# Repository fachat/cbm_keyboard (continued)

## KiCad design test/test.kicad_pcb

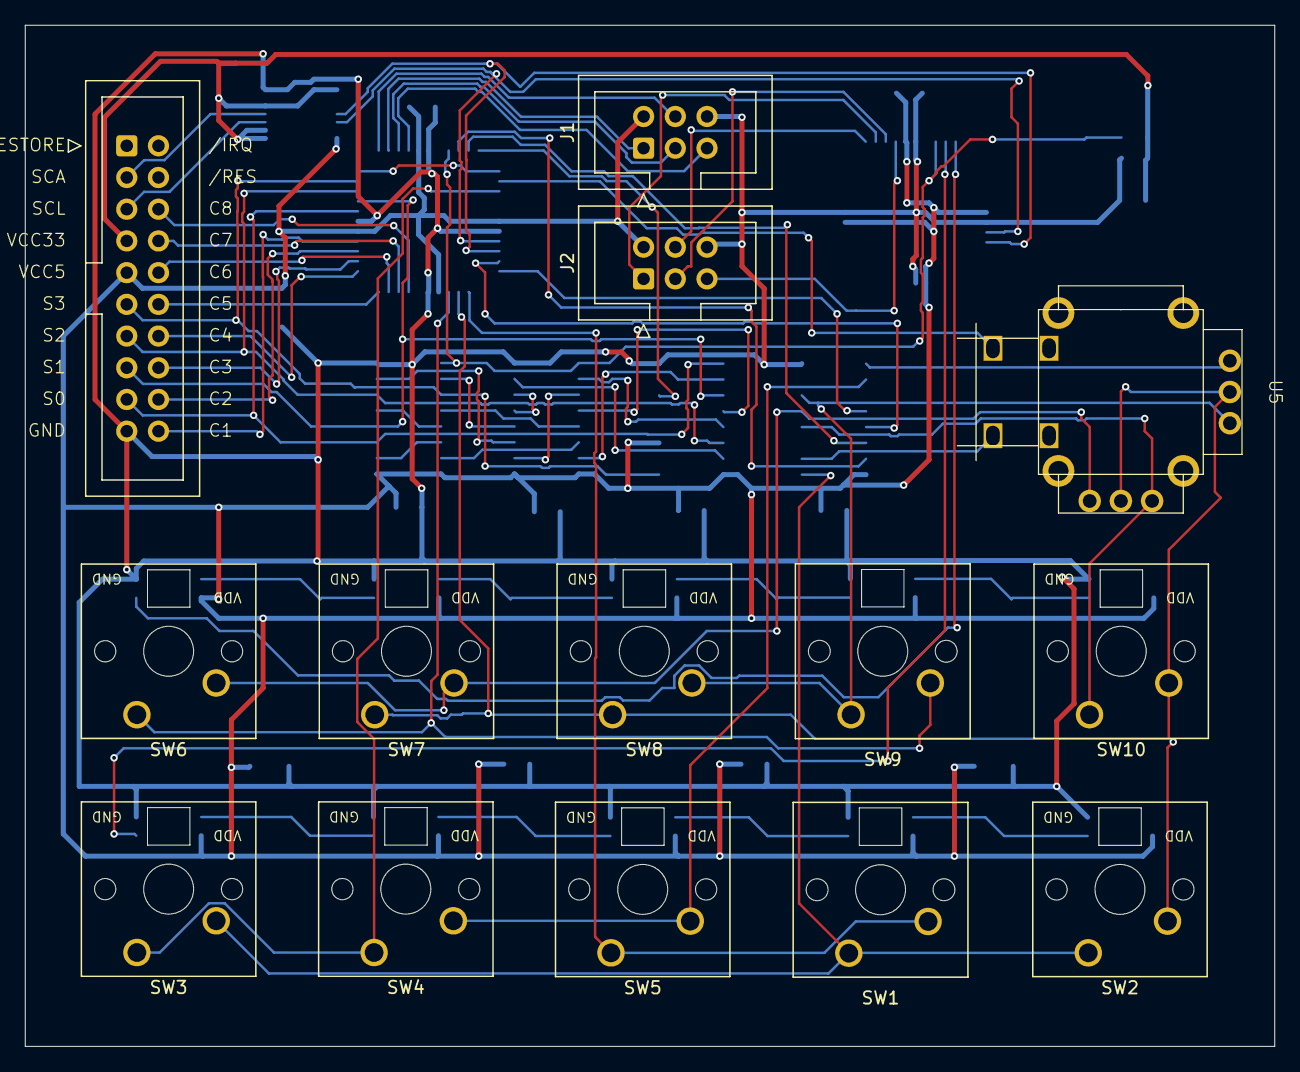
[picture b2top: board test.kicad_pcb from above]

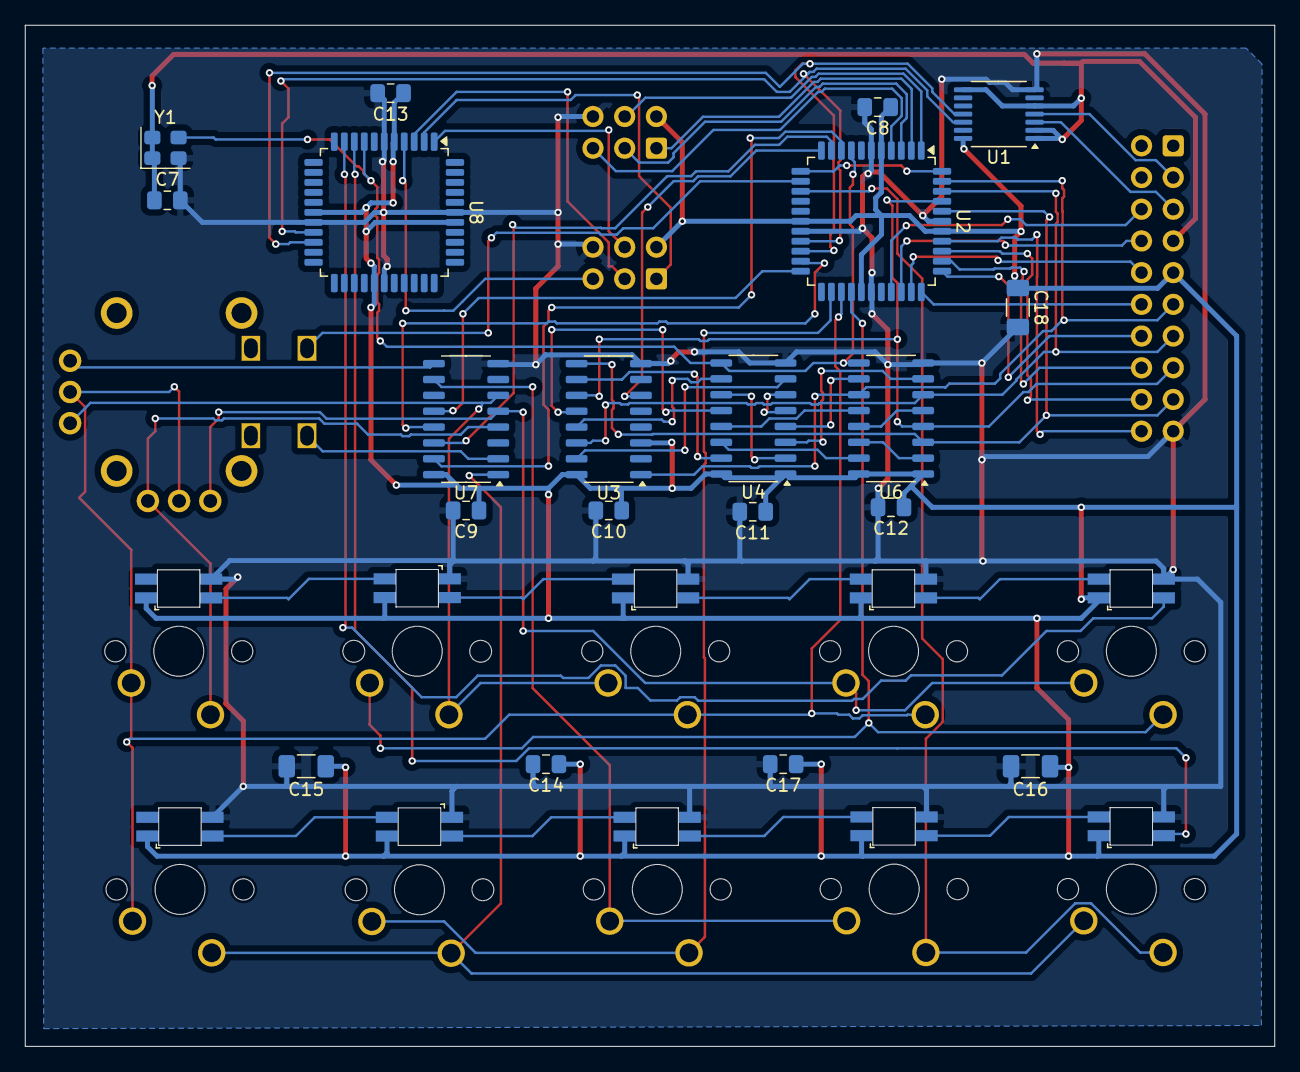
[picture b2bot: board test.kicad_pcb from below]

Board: 2 copper layers, 100.1 x 81.8 mm, 34 parts (20 on the bottom side), 68 nets.

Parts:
C7, C8, C9, C10, C11, C12, C13, C14, C17: 100n; C_0805_2012Metric_Pad1.18x1.45mm_HandSolder
C15, C16, C18: 100u; C_1206_3216Metric_Pad1.33x1.80mm_HandSolder
J1, J2: AVR-ISP-6; IDC-Header_2x03_P2.54mm_Vertical
J6: New_PET_keyboard_connector; PET_New_Keyboard_Connector
SW1, SW9: CherryMX_1.00u_PCB_LTST-A683CEGBW-Rotated
SW2, SW10: CherryMX_LTST-A683CEGBW; SW_Cherry_MX_1.00u_PCB_with_RGB_LED
SW3, SW4, SW5, SW6, SW7, SW8: SW_Cherry_MX_1.00u_PCB_with_RGB_LED
U1: LSF0204Q; TSSOP-14_4.4x5mm_P0.65mm
U2, U8: ATmega32A-A; TQFP-44_10x10mm_P0.8mm
U3: 74HCT85; SO-16_3.9x9.9mm_P1.27mm
U4, U6: 74LS174; SO-16_3.9x9.9mm_P1.27mm
U5: THB Miniature Thumbstick THB001P
U7: 74LS145; SO-16_3.9x9.9mm_P1.27mm
Y1: ASE-xxxMHz; Oscillator_SMD_Abracon_ASE-4Pin_3.2x2.5mm

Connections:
C1: J6.20 (C1), U2.37 (PA0)
C2: J6.19 (C2), U2.36 (PA1)
C3: J6.18 (C3), U2.35 (PA2)
C4: J6.17 (C4), U2.34 (PA3)
C5: J6.16 (C5), U2.33 (PA4)
C6: J6.15 (C6), U2.32 (PA5)
C7: J6.14 (C7), U2.31 (PA6)
C8: J6.13 (C8), U2.30 (PA7)
CLK16M: U2.8 (XTAL1), U4.9 (Cp), U6.9 (Cp), U8.8 (XTAL1), Y1.3 (OUT)
Col1: SW1.1, SW5.1, U2.24 (PC5)
Col2: SW2.2, SW7.1, SW8.1, SW10.2, U2.25 (PC6), U5.10 (LRCommon), U5.13 (UDCommon)
Col3: SW6.1, SW9.1, U2.26 (PC7)
Col4: U2.13 (PD4), U5.7 (SW2_A)
Col5: SW3.1, SW4.1, U2.14 (PD5)
GND: C7.2, C8.2, C9.2, C10.2, C11.2, C12.2, C13.2, C14.2, C15.2, C16.2, C17.2, C18.2, J1.6 (GND), J2.6 (GND), J6.21 (GND), SW1.3 (GND), SW2.3 (VSS), SW3.3 (GND), SW4.3 (GND), SW5.3 (GND), SW6.3 (GND), SW7.3 (GND), SW8.3 (GND), SW9.3 (GND), SW10.3 (VSS), U1.7 (GND), U2.6 (GND), U2.18 (GND), U2.28 (GND), U2.39 (GND), U3.8 (GND), U4.8 (GND), U6.8 (GND), U7.8 (GND), U8.6 (GND), U8.18 (GND), U8.28 (GND), U8.39 (GND), Y1.2 (GND)
unnamed: J1.1 (MISO), U2.2 (PB6)
unnamed: J1.4 (MOSI), U2.1 (PB5)
unnamed: J1.3 (SCK), U2.3 (PB7)
unnamed: J1.5 (~RST), U2.4 (~RESET)
unnamed: J2.1 (MISO), U8.2 (PB6)
unnamed: J2.4 (MOSI), U8.1 (PB5)
unnamed: J2.3 (SCK), U8.3 (PB7)
unnamed: J2.5 (~RST), U8.4 (~RESET)
unnamed: J6.29 (SCA), U1.4 (A3)
unnamed: J6.28 (SCL), U1.3 (A2)
unnamed: SW1.4 (DIN), SW5.5 (DOUT)
unnamed: SW1.5 (DOUT), SW2.4 (DIN)
unnamed: SW3.4 (DIN), U8.9 (PD0)
unnamed: SW3.5 (DOUT), SW4.4 (DIN)
unnamed: SW4.5 (DOUT), SW5.4 (DIN)
unnamed: SW6.4 (DIN), U8.10 (PD1)
unnamed: SW6.5 (DOUT), SW7.4 (DIN)
unnamed: SW7.5 (DOUT), SW8.4 (DIN)
unnamed: SW8.5 (DOUT), SW9.4 (DIN)
unnamed: SW9.5 (DOUT), SW10.4 (DIN)
unnamed: U2.12 (PD3), U2.44 (PB4)
unnamed: U2.21 (PC2), U7.13 (P2)
unnamed: U2.22 (PC3), U7.12 (P3)
unnamed: U2.9 (PD0), U7.15 (P0)
unnamed: U2.10 (PD1), U7.14 (P1)
unnamed: U2.11 (PD2), U3.6 (Oa=b)
unnamed: U3.10 (A0), U4.15 (Q5)
unnamed: U3.12 (A1), U4.12 (Q4)
unnamed: U3.13 (A2), U4.10 (Q3)
unnamed: U3.15 (A3), U4.7 (Q2)
unnamed: U4.3 (D0), U6.7 (Q2)
unnamed: U4.4 (D1), U6.10 (Q3)
unnamed: U4.5 (Q1), U4.6 (D2)
unnamed: U4.2 (Q0), U4.11 (D3)
unnamed: U4.13 (D4), U6.12 (Q4)
unnamed: U4.14 (D5), U6.15 (Q5)
unnamed: U6.5 (Q1), U6.13 (D4)
unnamed: U6.2 (Q0), U6.14 (D5)
Row0: SW1.2, SW2.1, SW3.2, U7.1 (Q0)
Row1: U5.8 (SW2_B), U7.2 (Q1)
Row3: SW10.1, U5.12 (Up), U7.4 (Q3)
Row4: SW6.2, SW7.2, U5.14 (Down), U7.5 (Q4)
Row5: SW8.2, SW9.2, U5.11 (Right), U7.6 (Q5)
Row7: U5.9 (Left), U7.9 (Q7)
Row8: SW4.2, SW5.2, U7.10 (Q8)
S0: J6.22 (S0), U2.40 (PB0), U3.9 (B0), U6.3 (D0)
S1: J6.23 (S1), U2.41 (PB1), U3.11 (B1), U6.4 (D1)
S2: J6.24 (S2), U2.42 (PB2), U3.14 (B2), U6.6 (D2)
S3: J6.25 (S3), U2.43 (PB3), U3.1 (B3), U6.11 (D3)
SCL: U1.12 (B2), U2.19 (PC0), U8.19 (PC0)
SDA: U1.11 (B3), U2.20 (PC1), U8.20 (PC1)
V33: C7.1, J6.27 (VCC33), U1.1 (VRefA), U1.2 (A1), U1.5 (A4), U1.8 (EN), Y1.1 (EN), Y1.4 (Vdd)
VCC: C8.1, C9.1, C10.1, C11.1, C12.1, C13.1, C14.1, C15.1, C16.1, C17.1, C18.1, J1.2 (VCC), J2.2 (VCC), J6.26 (VCC5), SW1.6 (VCC), SW2.6 (VDD), SW3.6 (VCC), SW4.6 (VCC), SW5.6 (VCC), SW6.6 (VCC), SW7.6 (VCC), SW8.6 (VCC), SW9.6 (VCC), SW10.6 (VDD), U1.14 (VRefB), U2.5 (VCC), U2.17 (VCC), U2.27 (AVCC), U2.38 (VCC), U3.3 (Ia=b), U3.16 (VCC), U4.1 (~Mr), U4.16 (VCC), U6.1 (~Mr), U6.16 (VCC), U7.16 (VCC), U8.5 (VCC), U8.17 (VCC), U8.27 (AVCC), U8.38 (VCC)

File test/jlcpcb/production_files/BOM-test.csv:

Comment,Designator,Footprint,LCSC,Quantity
ASE-xxxMHz,Y1,Oscillator_SMD_Abracon_ASE-4Pin_3.2x2.5mm,C12668,1
100n,"C10,C11,C12,C13,C14,C17,C7,C8,C9",C_0805_2012Metric_Pad1.18x1.45mm_HandSolder,C14663,9
100u,"C15,C16,C18",C_1206_3216Metric_Pad1.33x1.80mm_HandSolder,C15008,3
LSF0204Q,U1,TSSOP-14_4.4x5mm_P0.65mm,C2677502,1
~,U5,THB Miniature Thumbstick THB001P,C2685355,1
New_PET_keyboard_connector,J6,PET_New_Keyboard_Connector,C492444,1
~,"SW1,SW10,SW2,SW3,SW4,SW5,SW6,SW7,SW8,SW9",CherryMX_1.00u_PCB_LTST-A683CEGBW-Rotated,C5149201,10
AVR-ISP-6,"J1,J2",IDC-Header_2x03_P2.54mm_Vertical,C5372863,2
ATmega32A-A,"U2,U8",TQFP-44_10x10mm_P0.8mm,C5659,2
74HCT85,U3,SO-16_3.9x9.9mm_P1.27mm,C5953,1
74LS145,U7,SO-16_3.9x9.9mm_P1.27mm,C60829,1
74LS174,"U4,U6",SO-16_3.9x9.9mm_P1.27mm,C6828,2

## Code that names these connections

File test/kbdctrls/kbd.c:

#include <string.h>
#include <util/delay.h>
#include <avr/io.h>
#include <avr/interrupt.h>

#include "kbd.h"

unsigned char rowvals[16];

/*
 * Connection to the actual host
 */
void host_setup() {

	memset(rowvals, 0, 16);

	// disable UART (alt fun conflicts with I/O)
	UCSRB = 0;
	// JTAG needs to be disabled by HFUSE

	// port B0-3 is select lines in from host
	DDRB &= 0xf0;
	// no pullups
	PORTB &= 0xf0;
	// PB 5-7 are SPI prog lines, doubling as output to Host
	// test for moving PA0-7 to PB0-7
	DDRB &= 0x1f;
	// no pullups, set to output 0 when active to pull low
	PORTB & 0x1f;

	// PB4 is output to /RES when pulled low
	PORTB |= 0x10;
	DDRB |= 0x10;

	// PA is column out, using open-collector
	// no pullups. So, output is sent by
	// setting port to 0, and input.
	// then switching to output 
	// for those bits that should be pulled low
	DDRA = 0;
	PORTA = 0; 

	// interrupt handling
	// PD2 and PD3 are interrupt sources, PD2 is INT0 
	// and used as host select change int
	DDRD &= 0xfb;
	// no pullups
	PORTD &= 0xfb;

	// configure int0 on falling edge
	MCUCR = (MCUCR & 0xfc) | 0x02;
	// enable int0
	GICR |= 0x40;

	// own keyboard scan

	// row select bits 0/1
	DDRD |= 0x03;
	PORTD &= 0xfc;
	// row select bits 2/3
	DDRC |= 0x0c;
	PORTC &= 0xf3;

	// column value inputs
	// split on two ports due to needed alt functions for PC0/1, PD2

	// bits 0-3 are PC4-7, input with pullup
	DDRC &= 0x0f;
	PORTC |= 0xf0;
	// bits 4-7 are PD4-7, input with pullup
	DDRD &= 0x0f;
	PORTD |= 0xf0;

	// set PA0 to analog input,

	// AREF = AVCC
	// left adjust so we only need to use the
	// high byte with 8 bit resolution
	ADMUX = 0x60;
	// enable ADC, single ended PA0
	ADCSRA = 0x80;

	sei();
}

/*
 * note this ISR sets DDRA in less than 2.3us
 * which is very much enough for a 1-4 MHz PET scan routine
 * but not for a 13.5 MHz speed machine. 
 *
 * The normal scan reads the byte, then compares it again.
 * The first read happens on cycle 8 after change, the second on cycle 11.
 * See $e4be and following in the BASIC 4
 *
 * So, we have 11 cycles at 13.5 MHz, or 810ns only to write the correct
 * value ...
 *
 */
ISR( INT0_vect ) {
	DDRA = rowvals[PINB & 0x0f] & 0xfe;
	//PORTD ^= 0x01;
}

void kbd_scan() {
	for (unsigned char row = 0; row < 16; row++) {
		// set row selector
		PORTD = (PORTD & 0xfc) | (row & 0x03);
		PORTC = (PORTC & 0xf3) | (row & 0x0c);

		// read col values for row
		unsigned char v = 0;
		unsigned char ind = PIND;
		unsigned char inc = PINC;
		v = (ind & 0xf0) | ((inc >> 4) & 0x0f);

		v |= 3; 

		rowvals[row] = v ^ 255;
	}
}

void check_res() {
	// check RES
	if (rowvals[9] & 0x20) {
		// res low
		PORTB &= 0xef;
	} else {
		PORTB |= 0x10;
	}
}

void joy_scan() {
	// prescaler 7 = 1/128 = 125kHz
	ADCSRA = 0x87;

	//start conversion
	ADCSRA |= 1 << ADSC;

	while (!(ADCSRA & 0x10)) {
		// ADIF set
	
		// we use left adjust, so only high byte needed	
		unsigned char val = ADCH;

		// max value is 0xff
		// mid value is 0x80
		// low water we define as 0x40
		// high water we set to 0xc0
		if (val < 0x40) {
			// set crsr down
			rowvals[1] |= 0x40;
			// set ">" 
			//rowvals[8] |= 0x10;
		} else
		if (val > 0xc0) {
			// set crsr up
			rowvals[1] |= 0x40;
			rowvals[8] |= 0x20;
			// set "<" 
			//rowvals[9] |= 0x08;
		}
	}	

}

void main() {

	host_setup();

	// fake key for test
	//rowvals[1] = 0x01;

	while (1) {
		kbd_scan();
		joy_scan();
		check_res();
		_delay_ms(10);
	}
}

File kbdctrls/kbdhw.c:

#include <string.h>
#include <util/delay.h>
#include <avr/io.h>
#include <avr/interrupt.h>

#include "kbdhw.h"
#include "map.h"

unsigned char scanvals[16];
static unsigned char rowvals[16];

/*
 * Connection to the actual host
 */
void host_setup() {

	memset(rowvals, 0, 16);

	// disable UART (alt fun conflicts with I/O)
	UCSRB = 0;
	// JTAG needs to be disabled by HFUSE

	// port A0-3 is select lines in from host
	DDRA &= 0xf0;
	// no pullups
	PORTA &= 0xf0;

	// PB 0-7 are "open collector" outputs; 
	// i.e. only set to output 0 when active, otherwise input
	// PB 5-7 are SPI prog lines, doubling as output to Host
	DDRB &= 0x00;
	// no pullups, set to output 0 when active to pull low
	PORTB &= 0x00;

	// PD3 is output to /RES when pulled low
	PORTD |= 0x08;
	DDRD |= 0x08;

	// interrupt handling
	// PD2 and PD3 are interrupt sources, PD2 is INT0 
	// and used as host select change int
	DDRD &= 0xfb;
	// no pullups
	PORTD &= 0xfb;

	// configure int0 on falling edge
	MCUCR = (MCUCR & 0xfc) | 0x02;
	// enable int0
	GICR |= 0x40;

	// own keyboard scan

	// row select bits 0/1 PD0/1
	DDRD |= 0x03;
	PORTD &= 0xfc;
	// row select bits 2/3 PC2/3
	DDRC |= 0x0c;
	PORTC &= 0xf3;

	// column value inputs
	// split on two ports due to needed alt functions for PC0/1, PD2

	// bits 0-3 are PC4-7, input with pullup
	DDRC &= 0x0f;
	PORTC |= 0xf0;
	// bits 4-7 are PD4-7, input with pullup
	DDRD &= 0x0f;
	PORTD |= 0xf0;

	// set PA0 to analog input,

	// AREF = AVCC
	// left adjust so we only need to use the
	// high byte with 8 bit resolution
	// select A7
	ADMUX = 0x67;
	// enable ADC
	ADCSRA = 0x80;

	sei();
}

/*
 * note this ISR sets DDRA in less than 2.3us
 * which is very much enough for a 1-4 MHz PET scan routine
 * but not for a 13.5 MHz speed machine. 
 *
 * The normal scan reads the byte, then compares it again.
 * The first read happens on cycle 8 after change, the second on cycle 11.
 * See $e4be and following in the BASIC 4
 *
 * So, we have 11 cycles at 13.5 MHz, or 810ns only to write the correct
 * value ...
 *
 */
ISR( INT0_vect ) {
	DDRB = rowvals[PINA & 0x0f];
	//PORTD ^= 0x01;
}

/*
 * set the RES line active to reset the host
 */
void set_reset(int reset) {
	if (reset) {
		// res low
		PORTD &= 0xf7;
	} else {
		PORTD |= 0x08;
	}
}

/*
 * scan the joystick
 */
void joy_scan() {
	unsigned char val;

	// prescaler 7 = 1/128 = 125kHz
	ADCSRA = 0x07;

	//ADCSRA |= 1 << ADEN;

	// --------------------------------------------
	// measure up/down

	ADMUX = 0x67;


	// disable interrupt flag
	ADCSRA |= 1 << ADIF;

	// enable conversion
	ADCSRA |= 1 << ADEN;

	//start conversion
	ADCSRA |= 1 << ADSC;

	while (ADCSRA & (1<<ADSC)) { }

		// ADSC done
	
		// we use left adjust, so only high byte needed	
		val = ADCH;

		// max value is 0xff
		// mid value is 0x80
		// low water we define as 0x40
		// high water we set to 0xc0
		if (val < 0x40) {
			// set crsr up
			scanvals[1] |= 0x40;
			scanvals[8] |= 0x20;
		} else
		if (val > 0xc0) {
			// set crsr down
			scanvals[1] |= 0x40;
		}
//	}
	
	// --------------------------------------------
	// measure left/right

	ADCSRA = 0x07;

	ADMUX = 0x66;

	// disable interrupt flag
	ADCSRA |= 1 << ADIF;

	ADCSRA |= 1 << ADEN;

	//start conversion
	ADCSRA |= 1 << ADSC;

	while (ADCSRA & (1<<ADSC)) { }
		// ADIF set
	
		// we use left adjust, so only high byte needed	
		val = ADCH;

		// max value is 0xff
		// mid value is 0x80
		// low water we define as 0x40
		// high water we set to 0xc0
		if (val < 0x40) {
			// set crsr right
			scanvals[0] |= 0x80;
		} else
		if (val > 0xc0) {
			// set crsr left
			scanvals[0] |= 0x80;
			scanvals[8] |= 0x20;
		}
	//}	
}

void key_swap() {

	memcpy(rowvals, scanvals, sizeof(rowvals));
}

void scan_clear() {

	memset(scanvals, 0, sizeof(rowvals));
}

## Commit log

2025-01-15 initial readme
2025-01-15 added keycap files, images
2025-01-15 fix gallery links; add link to keycaps open project
2025-01-15 add Makefile for call from family Makefile
2025-03-13 add STLs for keyboard support
2025-05-26 added Steve's PET-N keyboard, converted to kicad 9 (untested)
2025-05-31 first work on adding LEDs and extended connector
2025-06-01 add extension page, add 4-to-10 decoder
2025-06-01 add joystick footprints
2025-06-15 test board for LED drivers
2025-08-11 work on R3 of keyboard pcb
2025-08-12 initial placement
2025-08-12 PET-N r3
2025-08-22 work on 2nd update test
2025-08-23 production test pcb
2025-08-23 add LSCS parts numbers
2025-08-24 prod files as submitted
2025-09-06 add test prog for LED control on V3
2025-09-06 allow sending key programs to the atmega via I2C
2025-09-06 first test injecting a key using an atmega
2025-09-07 make kbd ctrl work (< 13MHz)
2025-09-07 update initial led test pattern
2025-09-17 new schematics version mainly complete
2025-09-17 remove old schem
2025-09-18 first layout
2025-09-22 layout work
2025-09-28 petn layout work
2025-09-30 more layout work
2025-10-01 add missing pcb trace
2025-10-05 almost done routing; last checks still open
2025-10-06 test program after converting PA0 to analog input for joystick
2025-10-06 fix Cn vs CCn bug, add proper joystick in schem; routing still to fix
2025-10-11 hopefully final schem and layout for 3.0A
2025-10-11 allow resetting the machine via the IDC connector's /RES line
2025-10-12 small layout updates, jlcpcb production files
2025-10-14 as sent to production
2025-11-01 LED and keyboard controller for the new pet-n-3.0a
2025-11-02 finishing R3.0
2025-11-02 cleanup
2025-11-02 fix the two 3.0A issues (temporarily)
2025-11-05 refactor LED ctrl into multiple files
2025-11-05 led controller understands single keypress
2025-11-05 fix kbd controller
2025-11-05 factor out kbd scanner into own file
2025-11-05 map digits to upper kbd row
2025-11-05 kbd ctrl sends led commands
2025-11-06 fix LED address decoding
2025-11-06 use raw key presses instead of mapped ones in I2C, so HW mapping works
2025-11-10 added multi-key programs
2025-11-11 add logo prg
2025-11-11 allow to key controller to inject texts to the pet
2025-11-12 add selection to enable top digit row mapping with long srq press
2025-11-13 finished first rev for the keyboard controllers
2025-11-22 fix hand in i2c code
2026-01-02 make shift lock / reset work, with led display; fix hang
2026-01-05 improved error handling, hopefully fixing the hangs
2026-01-06 work on LED i2c
2026-01-06 allow sending kprogs from I2C
2026-01-30 first run on r3.1
2026-03-06 new key caps
2026-03-06 working on new layout
2026-03-08 final layout, production files for 3.1A
2026-03-08 fixed position file
2026-03-13 reset shift lock on reset condition
2026-03-13 scan joystick
2026-03-13 joystick in both directions
2026-04-05 add orientation marker for backlight LEDs and move to 3.1B
2026-04-18 add demo program for the key leds
2026-05-03 make kbd controller backward compat to rev 3.0 board; fix shift lock after reset bug
2026-05-08 add irq/nmi out
2026-06-23 move const table to Flash, to save RAM
